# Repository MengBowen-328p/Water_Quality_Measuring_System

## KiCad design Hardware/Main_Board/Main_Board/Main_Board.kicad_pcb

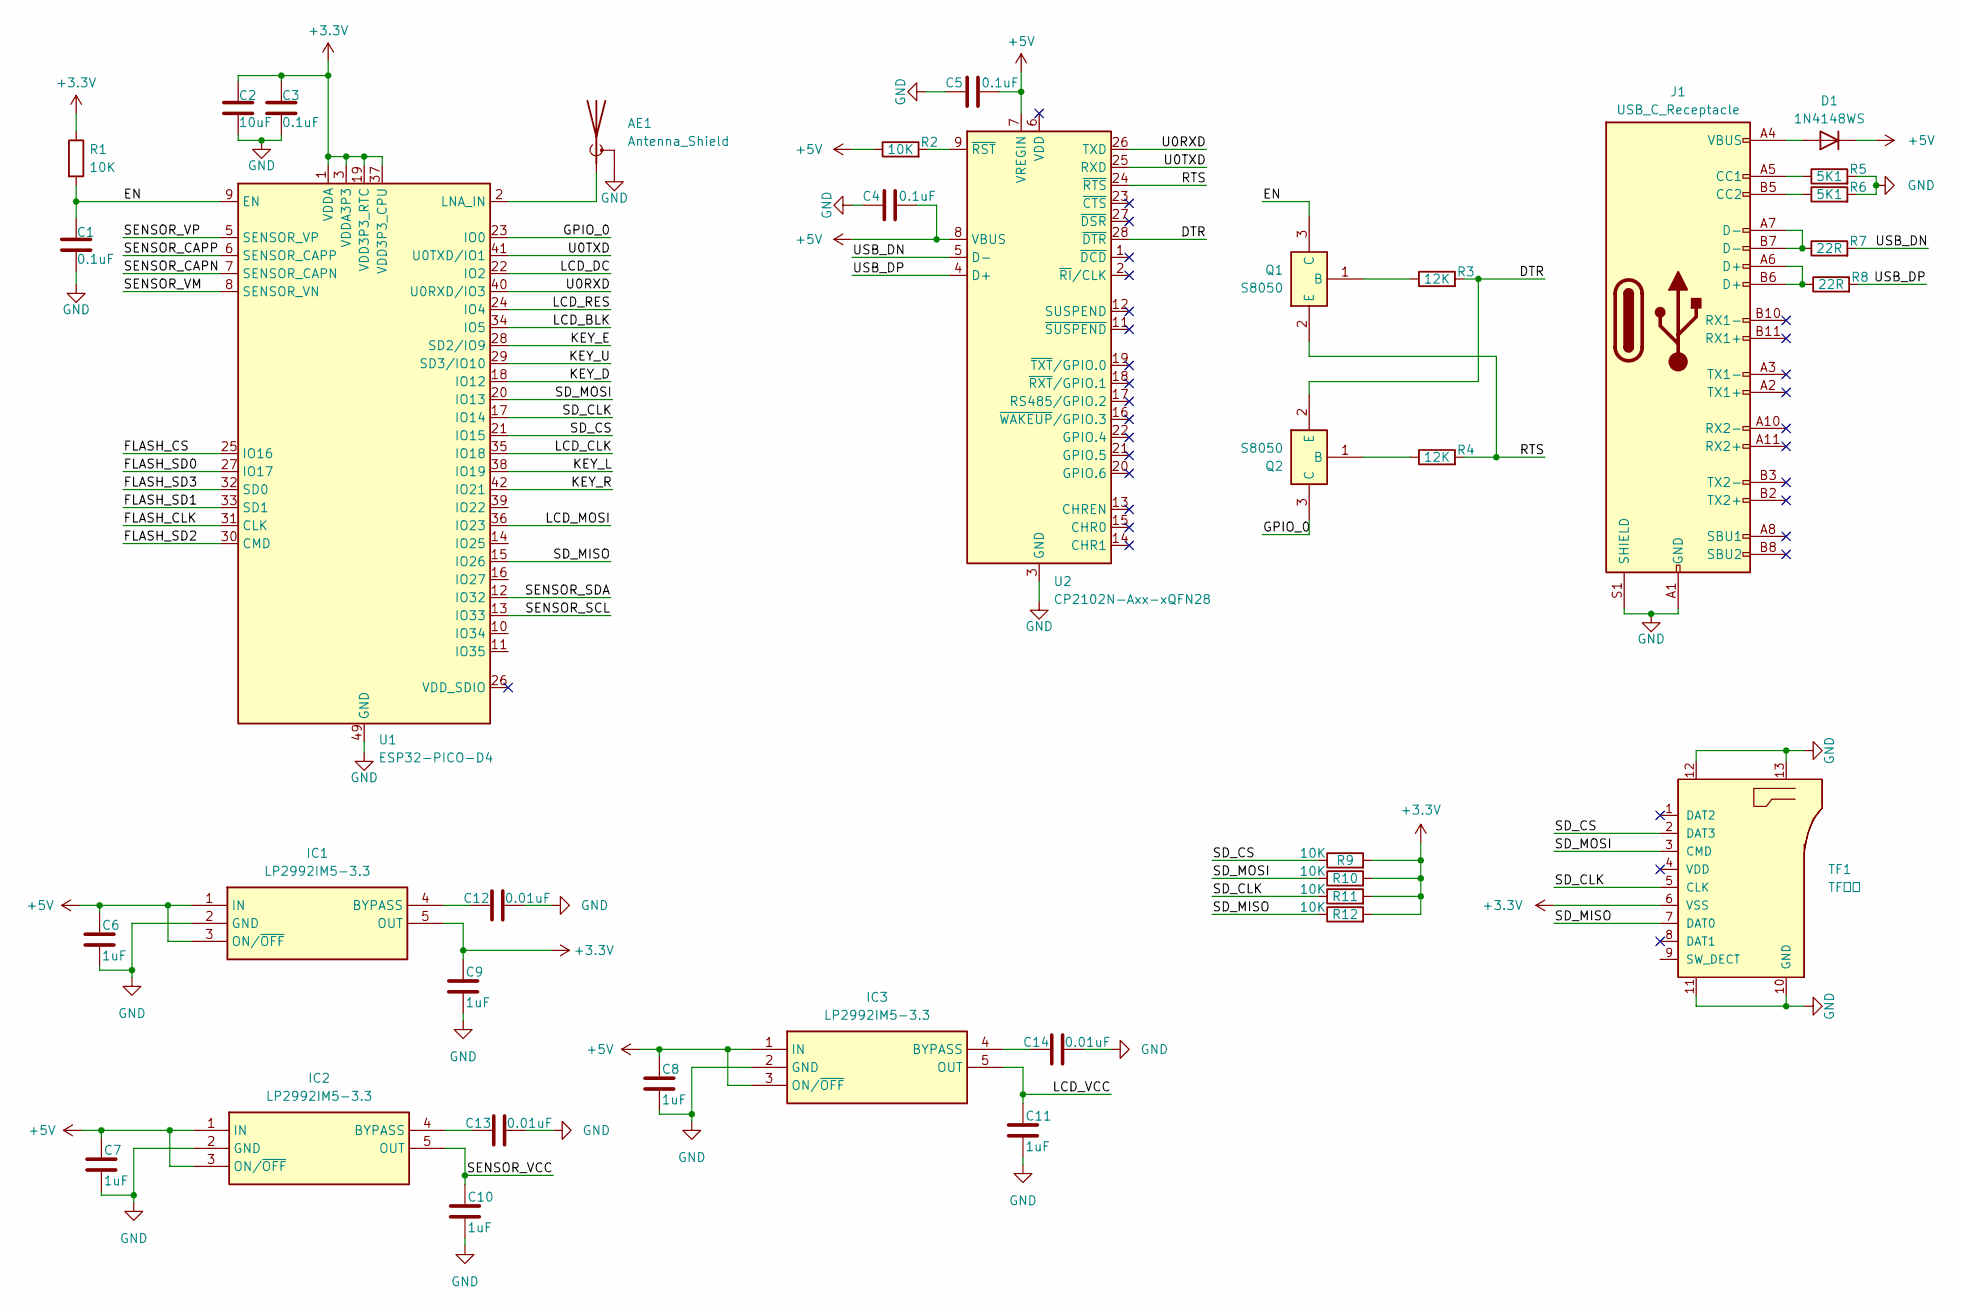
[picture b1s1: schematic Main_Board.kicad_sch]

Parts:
AE1: Antenna_Shield; Johanson_2450AT43F0100
C1, C3, C4, C5: 0.1uF; C_0603_1608Metric
C2: 10uF; C_0603_1608Metric
C6, C7, C8, C9, C10, C11: 1uF; C_0603_1608Metric
C12, C13, C14: 0.01uF; C_0603_1608Metric
D1: 1N4148WS; D_SOD-323
IC1, IC2, IC3: LP2992IM5-3.3; SOT95P280X145-5N; Manufacturer_Part_Number LP2992IM5-3.3; Mouser Part Number 926-LP2992IM5-33
J1: USB_C_Receptacle; USB_C_Receptacle_XKB_U262-16XN-4BVC11
Q1, Q2: S8050; SOT95P240X115-3N; Manufacturer_Part_Number S8050
R1, R2, R9, R10, R11, R12: 10K; R_0603_1608Metric
R3, R4: 12K; R_0603_1608Metric
R5, R6: 5K1; R_0603_1608Metric
R7, R8: 22R; R_0603_1608Metric
TF1: TF卡槽
U1: ESP32-PICO-D4; QFN-48-1EP_7x7mm_P0.5mm_EP5.3x5.3mm
U2: CP2102N-Axx-xQFN28; QFN-28-1EP_5x5mm_P0.5mm_EP3.35x3.35mm

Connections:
+3.3V: C2.1, C3.1, C9.1, IC1.5 (OUT), R1.1, R9.2, R10.2, R11.2, R12.2, U1.1 (VDDA), U1.3 (VDDA3P3), U1.4 (VDDA3P3), U1.19 (VDD3P3_RTC), U1.37 (VDD3P3_CPU), U1.43 (VDDA), U1.46 (VDDA)
+5V: C4.2, C5.2, C6.1, C7.1, C8.1, D1.1 (K), IC1.1 (IN), IC1.3 (ON/~OFF), IC2.1 (IN), IC2.3 (ON/~OFF), IC3.1 (IN), IC3.3 (ON/~OFF), R2.1, U2.7 (VREGIN), U2.8 (VBUS)
/DTR: Q2.2 (E), R3.2, U2.28 (~DTR)
/EN: C1.1, Q1.3 (C), R1.2, U1.9 (EN)
/FLASH_CLK: U1.31 (CLK)
/FLASH_CS: U1.25 (IO16)
/FLASH_SD0: U1.27 (IO17)
/FLASH_SD1: U1.33 (SD1)
/FLASH_SD2: U1.30 (CMD)
/FLASH_SD3: U1.32 (SD0)
/GPIO_0: Q2.3 (C), U1.23 (IO0)
/KEY_D: U1.18 (IO12)
/KEY_E: U1.28 (SD2/IO9)
/KEY_L: U1.38 (IO19)
/KEY_R: U1.42 (IO21)
/KEY_U: U1.29 (SD3/IO10)
/LCD_BLK: U1.34 (IO5)
/LCD_CLK: U1.35 (IO18)
/LCD_DC: U1.22 (IO2)
/LCD_MOSI: U1.36 (IO23)
/LCD_RES: U1.24 (IO4)
/LCD_VCC: C11.1, IC3.5 (OUT)
/RTS: Q1.2 (E), R4.2, U2.24 (~RTS)
/SD_CLK: R11.1, TF1.5 (CLK), U1.17 (IO14)
/SD_CS: R9.1, TF1.2 (DAT3), U1.21 (IO15)
/SD_MISO: R12.1, TF1.7 (DAT0), U1.15 (IO26)
/SD_MOSI: R10.1, TF1.3 (CMD), U1.20 (IO13)
/SENSOR_CAPN: U1.7 (SENSOR_CAPN)
/SENSOR_CAPP: U1.6 (SENSOR_CAPP)
/SENSOR_SCL: U1.13 (IO33)
/SENSOR_SDA: U1.12 (IO32)
/SENSOR_VCC: C10.1, IC2.5 (OUT)
/SENSOR_VM: U1.8 (SENSOR_VN)
/SENSOR_VP: U1.5 (SENSOR_VP)
/U0RXD: U1.40 (U0RXD/IO3), U2.26 (TXD)
/U0TXD: U1.41 (U0TXD/IO1), U2.25 (RXD)
/USB_DN: R7.2, U2.5 (D-)
/USB_DP: R8.2, U2.4 (D+)
GND: AE1.2 (Shield), C1.2, C2.2, C3.2, C4.1, C5.1, C6.2, C7.2, C8.2, C9.2, C10.2, C11.2, C12.2, C13.2, C14.2, IC1.2 (GND), IC2.2 (GND), IC3.2 (GND), J1.A1 (GND), J1.A12 (GND), J1.B1 (GND), J1.B12 (GND), J1.S1 (SHIELD), R5.2, R6.2, U1.49 (GND), U2.3 (GND), U2.29 (GND)
unnamed: AE1.1 (A), U1.2 (LNA_IN)
unnamed: D1.2 (A), J1.A4 (VBUS), J1.A9 (VBUS), J1.B4 (VBUS), J1.B9 (VBUS)
unnamed: C12.1, IC1.4 (BYPASS)
unnamed: C13.1, IC2.4 (BYPASS)
unnamed: C14.1, IC3.4 (BYPASS)
unnamed: J1.A5 (CC1), R5.1
unnamed: J1.B5 (CC2), R6.1
unnamed: J1.A6 (D+), J1.B6 (D+), R8.1
unnamed: J1.A7 (D-), J1.B7 (D-), R7.1
unnamed: Q1.1 (B), R3.1
unnamed: Q2.1 (B), R4.1
unnamed: R2.2, U2.9 (~RST)

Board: 2 copper layers, 36 parts (0 on the bottom side), 29 nets, no tracks yet.

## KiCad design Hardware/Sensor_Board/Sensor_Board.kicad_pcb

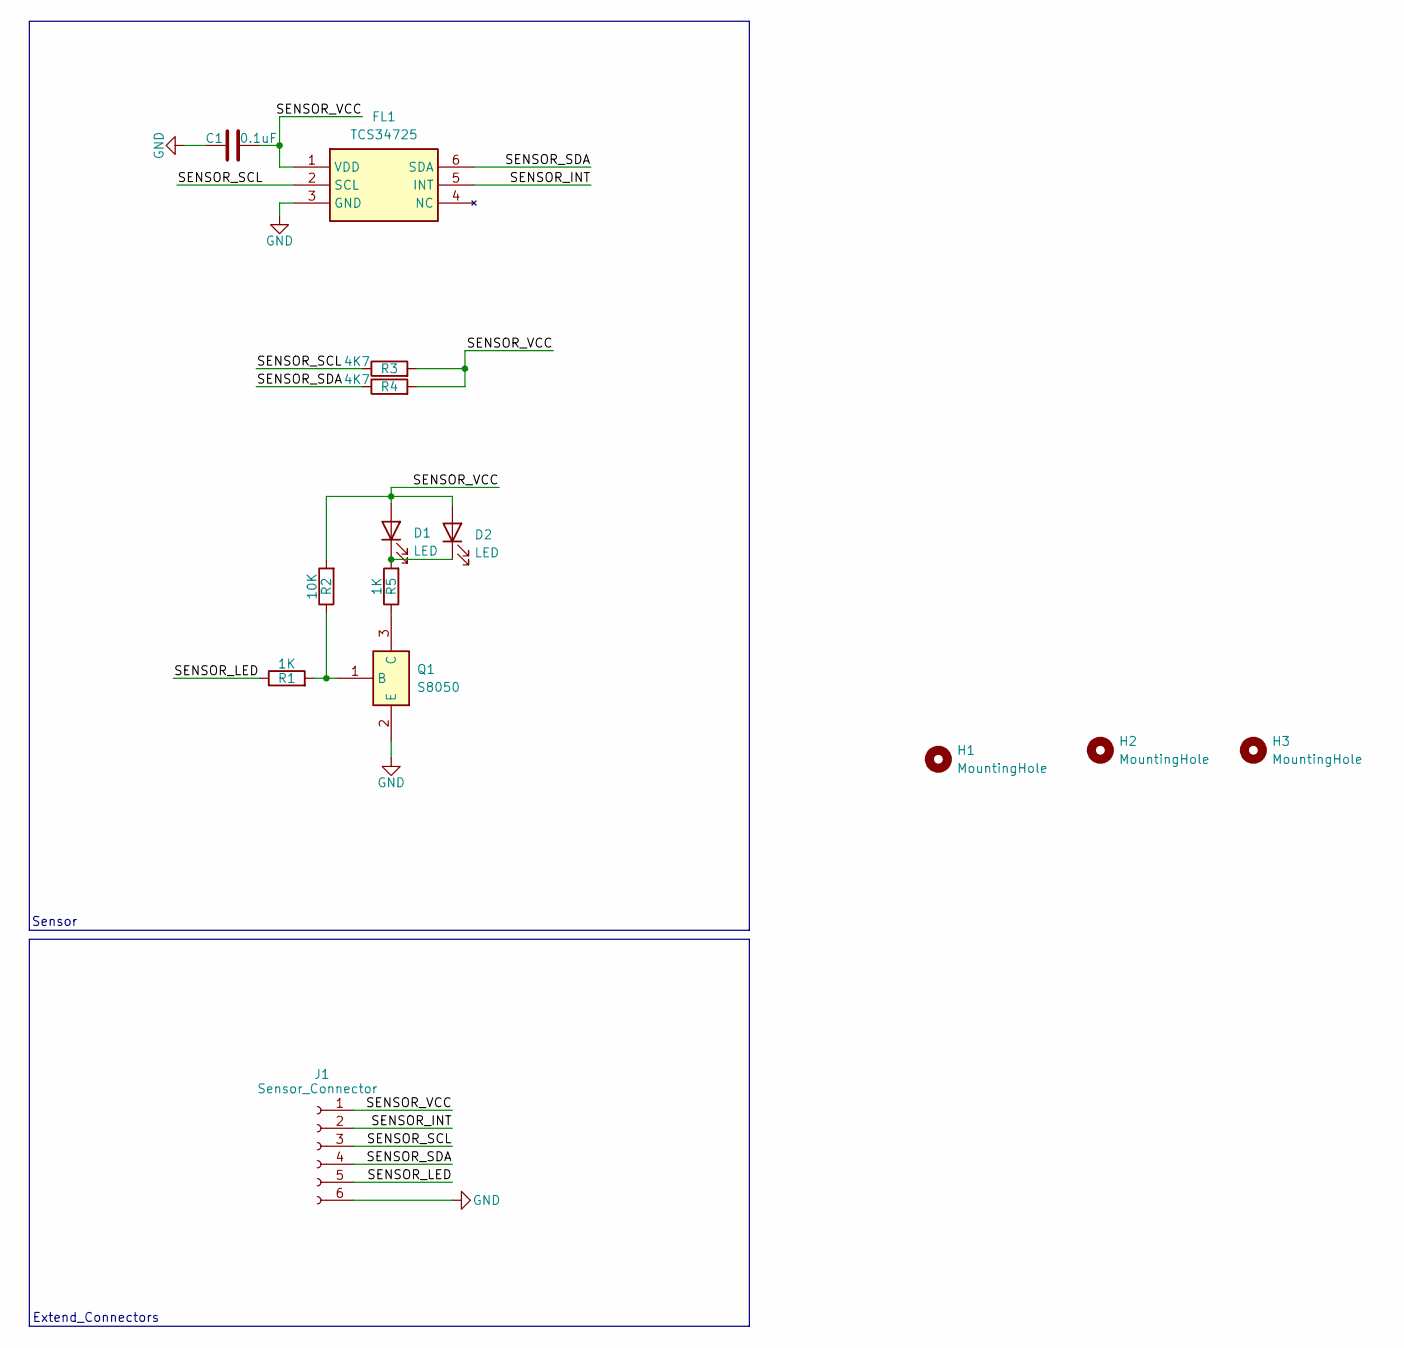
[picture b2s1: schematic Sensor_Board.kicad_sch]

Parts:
C1: 0.1uF; C_0603_1608Metric
D1, D2: LED; LED_RGB_5050-6
FL1: TCS34725; Manufacturer_Part_Number TCS34725
H1, H2, H3: MountingHole; MountingHole_2.2mm_M2
J1: Sensor_Connector; Hirose_FH12-6S-0.5SH_1x06-1MP_P0.50mm_Horizontal
Q1: S8050; SOT95P240X115-3N; Manufacturer_Part_Number S8050
R1, R5: 1K; R_0603_1608Metric
R2: 10K; R_0603_1608Metric
R3, R4: 4K7; R_0603_1608Metric

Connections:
/SENSOR_INT: FL1.5 (INT), J1.2
/SENSOR_LED: J1.5, R1.1
/SENSOR_SCL: FL1.2 (SCL), J1.3, R3.1
/SENSOR_SDA: FL1.6 (SDA), J1.4, R4.1
/SENSOR_VCC: C1.2, D1.2 (A), D2.2 (A), FL1.1 (VDD), J1.1, R2.2, R3.2, R4.2
GND: C1.1, FL1.3 (GND), J1.6, Q1.2 (E)
unnamed: D1.1 (K), D2.1 (K), R5.2
unnamed: Q1.1 (B), R1.2, R2.1
unnamed: Q1.3 (C), R5.1

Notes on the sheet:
Sensor
Extend_Connectors

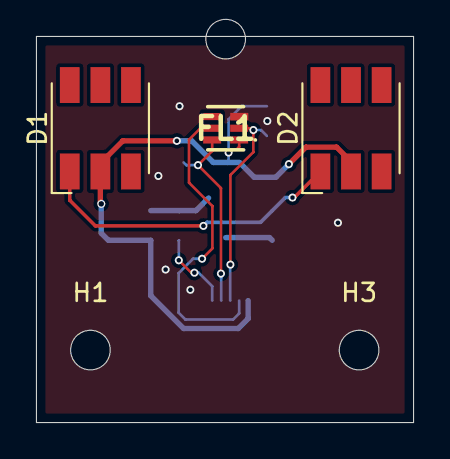
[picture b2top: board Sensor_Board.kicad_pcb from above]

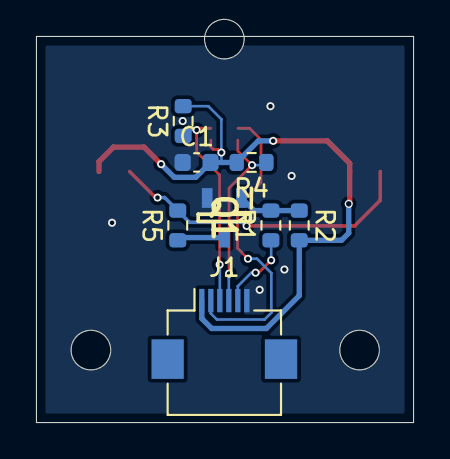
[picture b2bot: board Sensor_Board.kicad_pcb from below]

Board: 2 copper layers, 21.0 x 21.4 mm, 14 parts (8 on the bottom side), 9 nets.

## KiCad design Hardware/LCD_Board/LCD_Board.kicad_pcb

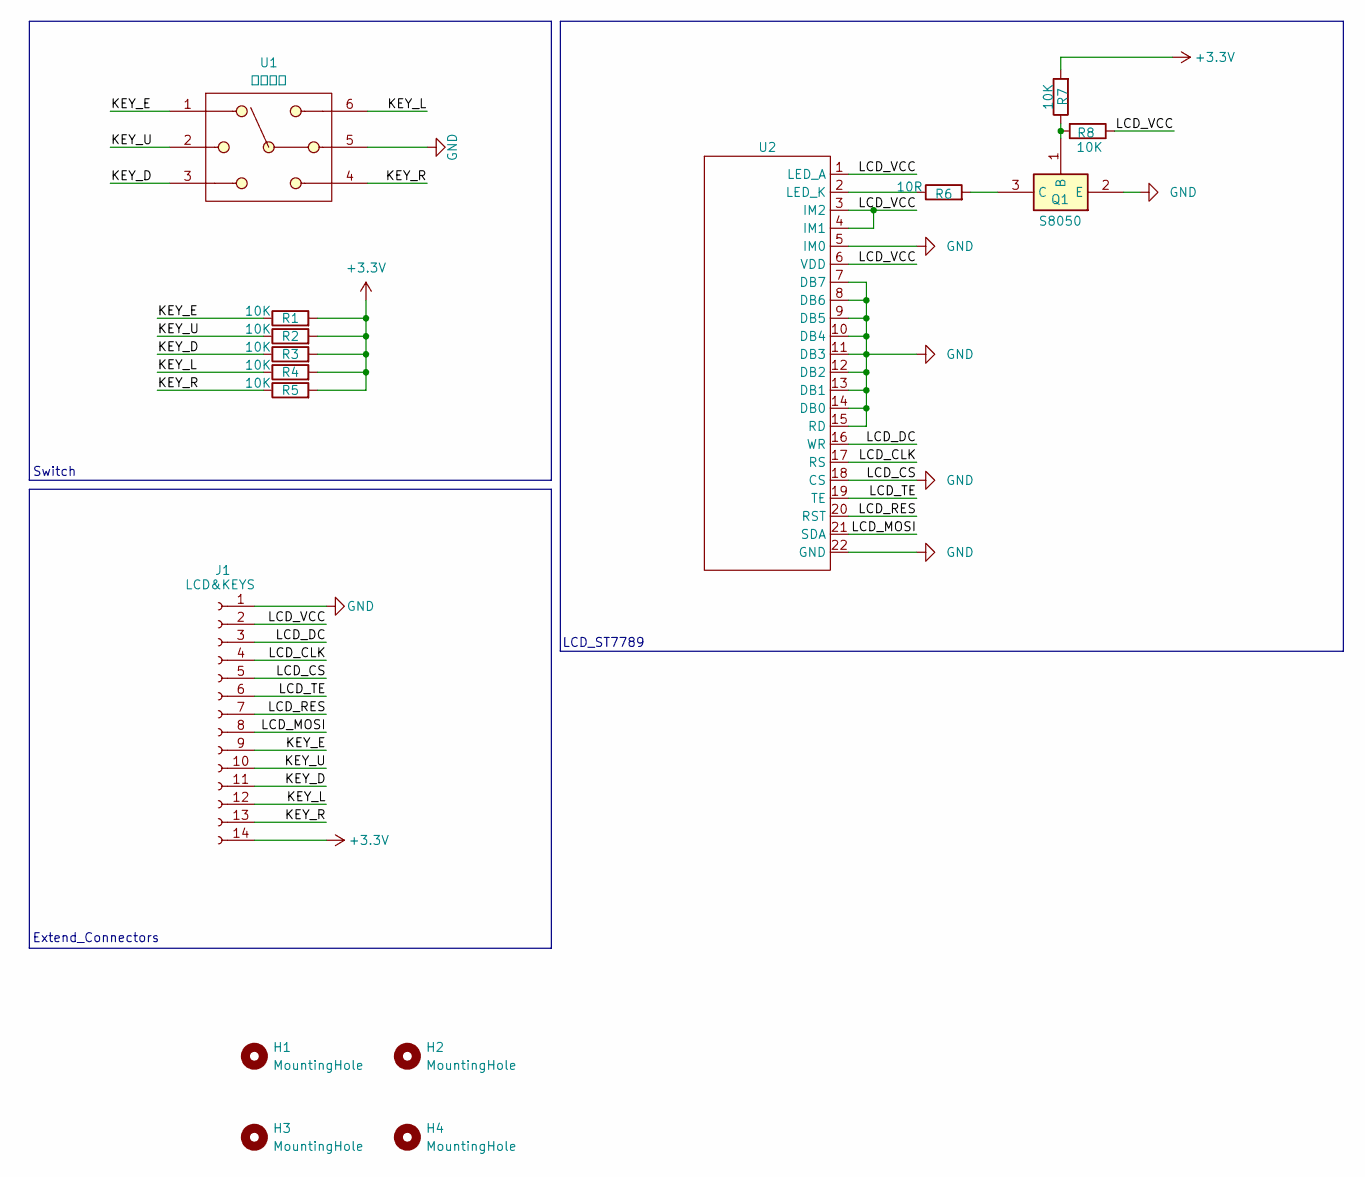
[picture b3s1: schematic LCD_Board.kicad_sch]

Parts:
H1, H2, H3, H4: MountingHole; MountingHole_2.2mm_M2
J1: LCD&KEYS; Hirose_FH12-14S-0.5SH_1x14-1MP_P0.50mm_Horizontal
Q1: S8050; SOT95P240X115-3N; Manufacturer_Part_Number S8050
R1, R2, R3, R4, R5, R7, R8: 10K; R_0603_1608Metric
R6: 10R; R_0603_1608Metric
U1: 五向开关
U2: ZJY200K-IF05

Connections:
+3.3V: J1.14, R1.2, R2.2, R3.2, R4.2, R5.2, R7.2
/KEY_D: J1.11, R3.1, U1.3
/KEY_E: J1.9, R1.1, U1.1
/KEY_L: J1.12, R4.1, U1.6
/KEY_R: J1.13, R5.1, U1.4
/KEY_U: J1.10, R2.1, U1.2
/LCD_CLK: J1.4, U2.17 (RS)
/LCD_DC: J1.3, U2.16 (WR)
/LCD_MOSI: J1.8, U2.21 (SDA)
/LCD_RES: J1.7, U2.20 (RST)
/LCD_TE: J1.6, U2.19 (TE)
/LCD_VCC: J1.2, R8.1, U2.1 (LED_A), U2.3 (IM2), U2.4 (IM1), U2.6 (VDD)
GND: J1.1, J1.5, Q1.2 (E), U1.5, U2.5 (IM0), U2.7 (DB7), U2.8 (DB6), U2.9 (DB5), U2.10 (DB4), U2.11 (DB3), U2.12 (DB2), U2.13 (DB1), U2.14 (DB0), U2.15 (RD), U2.18 (CS), U2.22 (GND)
unnamed: Q1.1 (B), R7.1, R8.2
unnamed: Q1.3 (C), R6.2
unnamed: R6.1, U2.2 (LED_K)

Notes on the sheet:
Extend_Connectors
LCD_ST7789
Switch

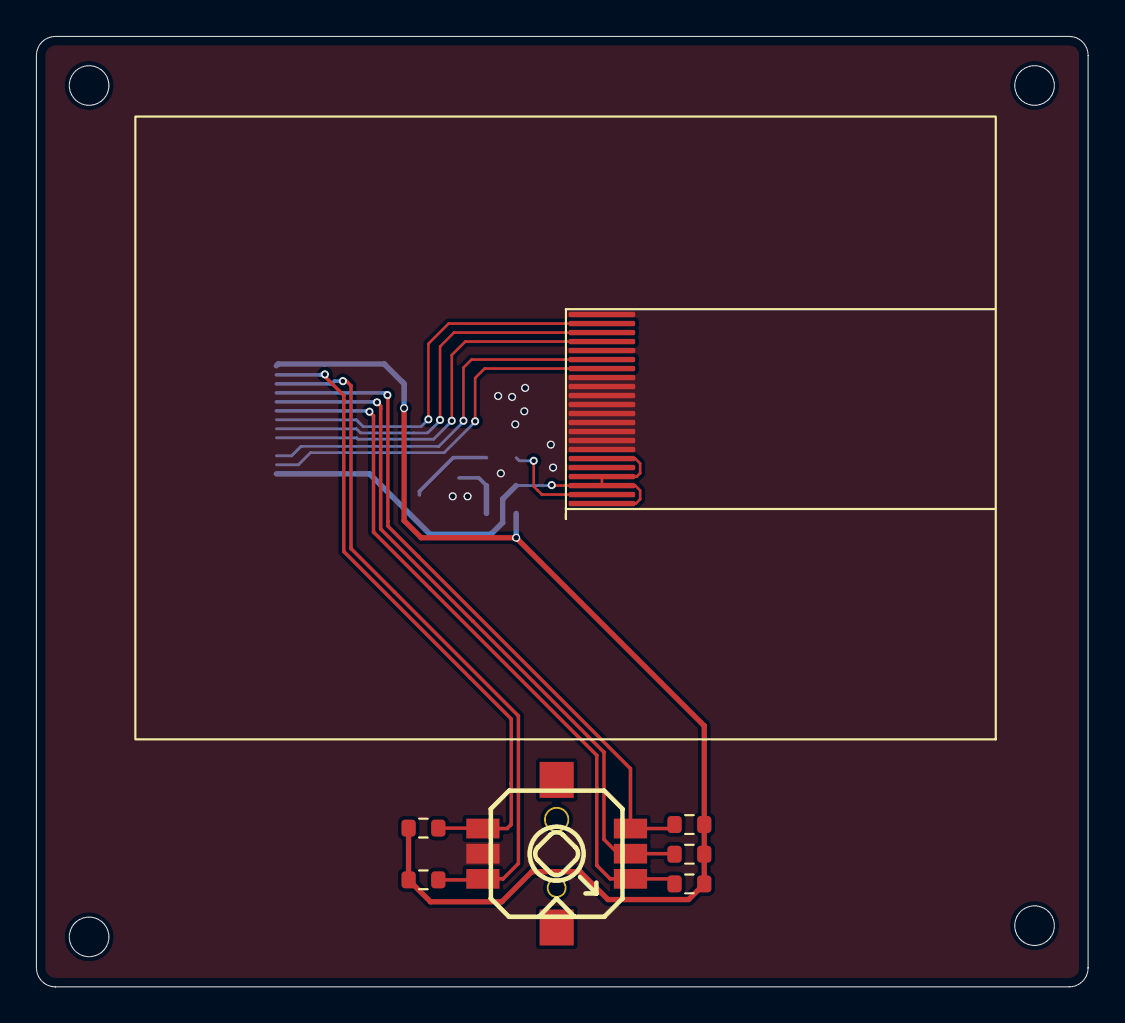
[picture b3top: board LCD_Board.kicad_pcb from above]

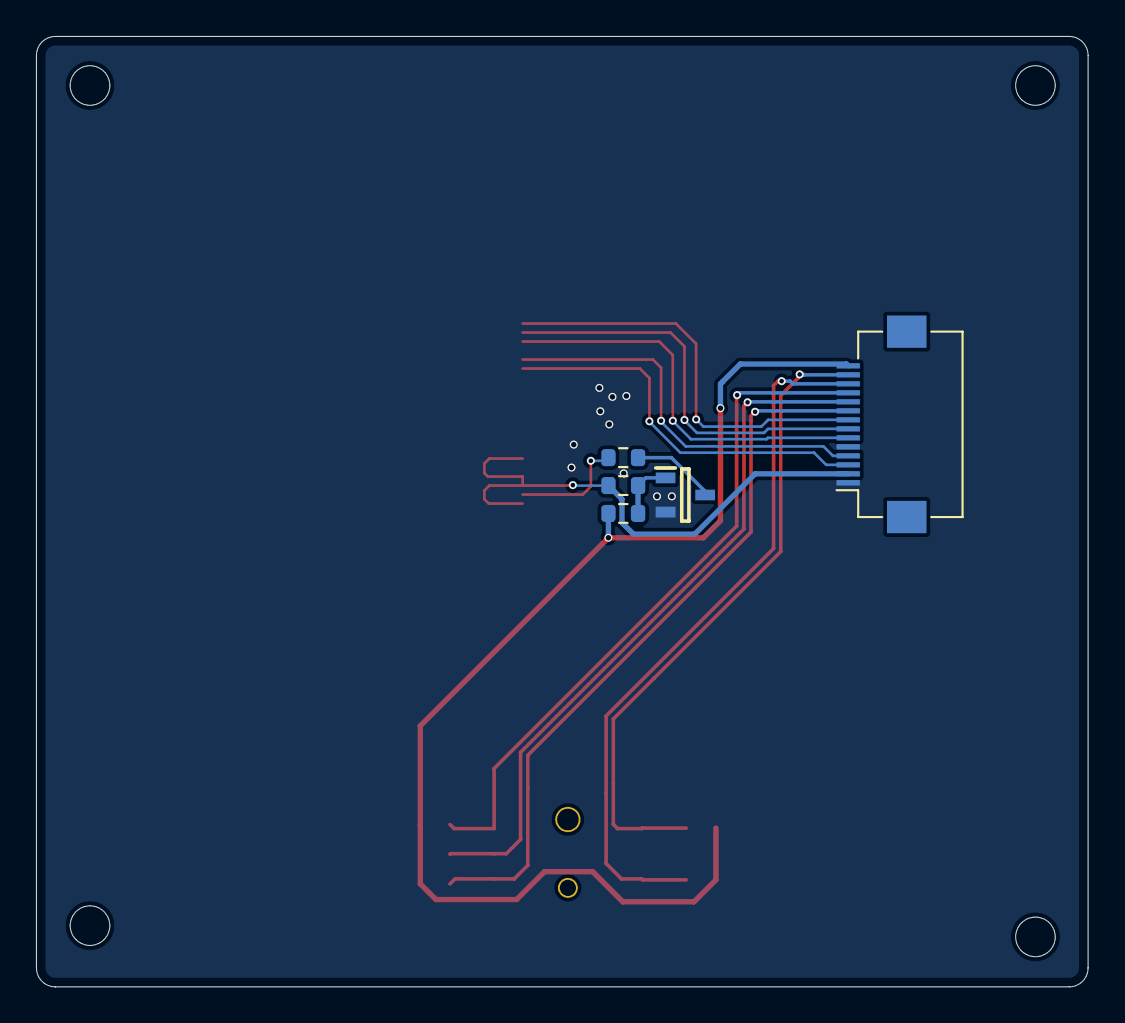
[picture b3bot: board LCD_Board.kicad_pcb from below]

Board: 2 copper layers, 58.4 x 52.8 mm, 16 parts (5 on the bottom side), 16 nets.

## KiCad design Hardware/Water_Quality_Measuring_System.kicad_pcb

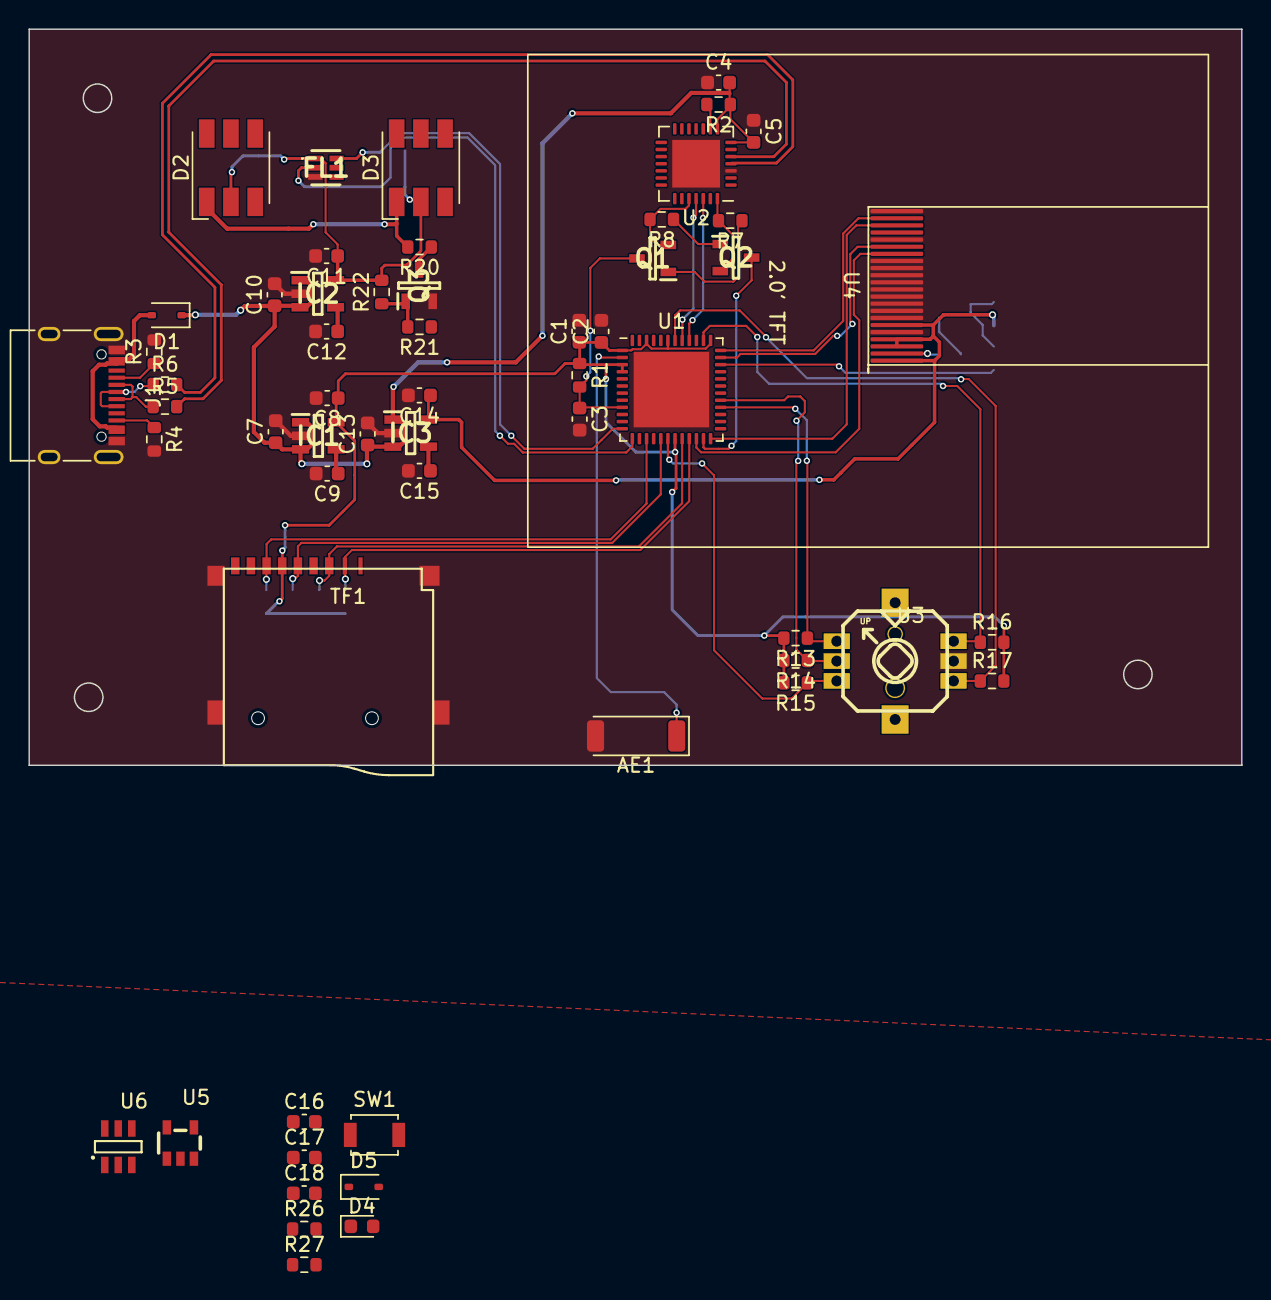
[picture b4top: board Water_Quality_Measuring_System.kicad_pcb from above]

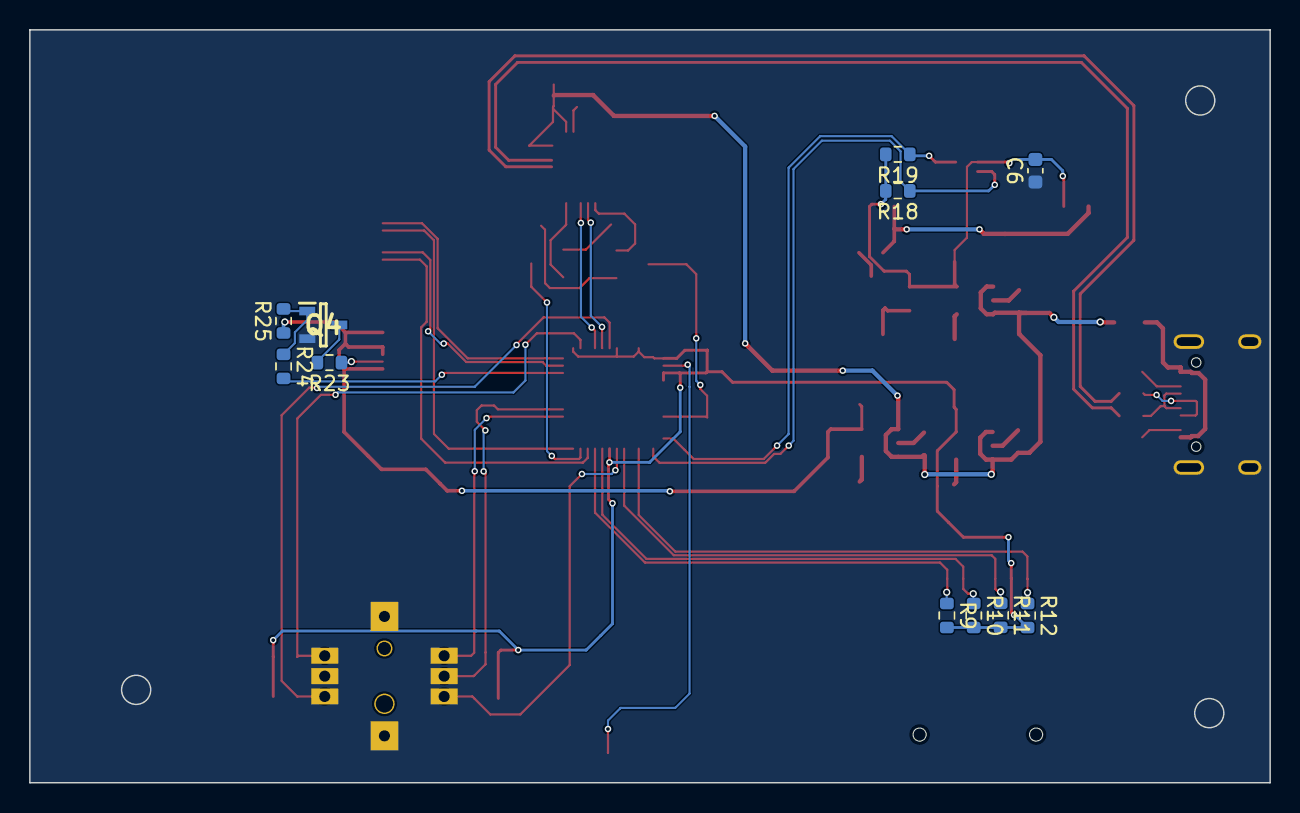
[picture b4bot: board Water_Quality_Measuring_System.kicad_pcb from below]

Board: 2 copper layers, 85.2 x 51.7 mm, 68 parts (11 on the bottom side), 53 nets.

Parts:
AE1: Antenna_Shield; Johanson_2450AT43F0100
C1, C3, C4, C5, C6: 0.1uF; C_0603_1608Metric
C2, C16, C18: 10uF; C_0603_1608Metric
C7, C8, C10, C11, C13, C14, C17: 1uF; C_0603_1608Metric
C9, C12, C15: 0.01uF; C_0603_1608Metric
D1: 1N4148WS; D_SOD-323
D2, D3: LED; LED_RGB_5050-6
D4: LED; LED_0603_1608Metric
D5: 1N5819WS; D_SOD-323
FL1: TCS34725
IC1, IC2, IC3: LP2992IM5-3.3; SOT95P280X145-5N
J1: USB_C_Receptacle; USB_C_Receptacle_XKB_U262-16XN-4BVC11
Q1, Q2, Q3, Q4: S8050; SOT95P240X115-3N
R1, R2, R9, R10, R11, R12, R13, R14, R15, R16, R17, R22, R24, R25, R26: 10K; R_0603_1608Metric
R3, R4: 5K1; R_0603_1608Metric
R5, R6: 22R; R_0603_1608Metric
R7, R8: 12K; R_0603_1608Metric
R18, R19: 4K7; R_0603_1608Metric
R20, R21: 1K; R_0603_1608Metric
R23: 10R; R_0603_1608Metric
R27: 1.66K; R_0603_1608Metric
SW1: Power; SW_SPST_B3U-1000P
TF1: TF卡槽
U1: ESP32-PICO-D4; QFN-48-1EP_7x7mm_P0.5mm_EP5.3x5.3mm
U2: CP2102N-Axx-xQFN28; QFN-28-1EP_5x5mm_P0.5mm_EP3.35x3.35mm
U3: 五向开关
U4: ZJY200K-IF05
U5: TP4055-42-SOT25-R; SOT-23-5_L2.9-W1.6-P0.95-LS2.8-BL
U6: EC190707; EC190707_STD

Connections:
+3.3V: C1.1, C2.1, C8.1, IC1.5 (OUT), R1.1, R9.2, R10.2, R11.2, R12.2, R13.2, R14.2, R15.2, R16.2, R17.2, TF1.6 (VSS), U1.1 (VDDA), U1.3 (VDDA3P3), U1.4 (VDDA3P3), U1.19 (VDD3P3_RTC), U1.37 (VDD3P3_CPU), U1.43 (VDDA), U1.46 (VDDA)
+5V: C4.2, C5.2, C17.2, D1.1 (K), R2.1, R26.1, U2.7 (VREGIN), U2.8 (VBUS), U5.4 (VCC)
/BAT+: C16.2, C18.2, U5.3 (BAT), U6.5 (VDD)
/BAT_OUT: C7.1, C10.1, C13.1, IC1.1 (IN), IC1.3 (ON/~OFF), IC2.1 (IN), IC2.3 (ON/~OFF), IC3.1 (IN), IC3.3 (ON/~OFF), U6.1 (OUT)
/DTR: Q2.2 (E), R7.2, U2.28 (~DTR)
/EN: C3.1, Q1.3 (C), R1.2, U1.9 (EN)
/GPIO_0: Q2.3 (C), U1.23 (IO0)
/KEY_D: R15.1, U1.18 (IO12), U3.3
/KEY_E: R13.1, U1.28 (SD2/IO9), U3.1
/KEY_L: R16.1, U1.38 (IO19), U3.6
/KEY_R: R17.1, U1.42 (IO21), U3.4
/KEY_U: R14.1, U1.29 (SD3/IO10), U3.2
/LCD_BLK: R24.2, U1.34 (IO5)
/LCD_CLK: U1.35 (IO18), U4.17 (RS)
/LCD_DC: U1.22 (IO2), U4.16 (WR)
/LCD_MOSI: U1.36 (IO23), U4.21 (SDA)
/LCD_RES: U1.24 (IO4), U4.20 (RST)
/LCD_VCC: C14.1, IC3.5 (OUT), R25.1, U4.1 (LED_A), U4.3 (IM2), U4.4 (IM1), U4.6 (VDD)
/RTS: Q1.2 (E), R8.2, U2.24 (~RTS)
/SD_CLK: R11.1, TF1.5 (CLK), U1.17 (IO14)
/SD_CS: R9.1, TF1.2 (DAT3), U1.21 (IO15)
/SD_MISO: R12.1, TF1.7 (DAT0), U1.15 (IO26)
/SD_MOSI: R10.1, TF1.3 (CMD), U1.20 (IO13)
/SENSOR_SCL: FL1.2 (SCL), R18.1, U1.13 (IO33)
/SENSOR_SDA: FL1.6 (SDA), R19.1, U1.12 (IO32)
/SENSOR_VCC: C6.2, C11.1, D2.2 (A), D3.2 (A), FL1.1 (VDD), IC2.5 (OUT), R18.2, R19.2, R22.2
/U0RXD: U1.40 (U0RXD/IO3), U2.26 (TXD)
/U0TXD: U1.41 (U0TXD/IO1), U2.25 (RXD)
/USB_DN: R5.2, U2.5 (D-)
/USB_DP: R6.2, U2.4 (D+)
GND: AE1.2 (Shield), C1.2, C2.2, C3.2, C4.1, C5.1, C6.1, C7.2, C8.2, C9.2, C10.2, C11.2, C12.2, C13.2, C14.2, C15.2, C16.1, C17.1, C18.1, D5.1 (K), FL1.3 (GND), IC1.2 (GND), IC2.2 (GND), IC3.2 (GND), J1.A1 (GND), J1.A12 (GND), J1.B1 (GND), J1.B12 (GND), J1.S1 (SHIELD), Q3.2 (E), Q4.2 (E), R3.2, R4.2, R27.2, SW1.1, TF1.10 (GND), TF1.11, TF1.12, TF1.13, U1.49 (GND), U2.3 (GND), U2.29 (GND), U3.5, U4.5 (IM0), U4.7 (DB7), U4.8 (DB6), U4.9 (DB5), U4.10 (DB4), U4.11 (DB3), U4.12 (DB2), U4.13 (DB1), U4.14 (DB0), U4.15 (RD), U4.18 (CS), U4.22 (GND), U5.2 (GND), U6.2 (GND)
unnamed: AE1.1 (A), U1.2 (LNA_IN)
unnamed: D1.2 (A), J1.A4 (VBUS), J1.A9 (VBUS), J1.B4 (VBUS), J1.B9 (VBUS)
unnamed: D2.1 (K), D3.1 (K), R20.2
unnamed: D4.2 (A), R26.2
unnamed: D4.1 (K), U5.1 (CHRG)
unnamed: D5.2 (A), SW1.2, U6.3 (KEY)
unnamed: C9.1, IC1.4 (BYPASS)
unnamed: C12.1, IC2.4 (BYPASS)
unnamed: C15.1, IC3.4 (BYPASS)
unnamed: J1.A5 (CC1), R3.1
unnamed: J1.B5 (CC2), R4.1
unnamed: J1.A6 (D+), J1.B6 (D+), R6.1
unnamed: J1.A7 (D-), J1.B7 (D-), R5.1
unnamed: Q1.1 (B), R7.1
unnamed: Q2.1 (B), R8.1
unnamed: Q3.1 (B), R21.2, R22.1
unnamed: Q3.3 (C), R20.1
unnamed: Q4.1 (B), R24.1, R25.2
unnamed: Q4.3 (C), R23.2
unnamed: R2.2, U2.9 (~RST)
unnamed: R23.1, U4.2 (LED_K)
unnamed: R27.1, U5.5 (PROG)

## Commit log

2024-01-10 Finished PCB Layout
2024-01-10 Init Firmware
2024-02-28 Finished Main Board PCB
2024-02-28 Finished All PCB
2024-03-01 Finished GUI Firmware
2024-03-02 Porting Input Device
2024-03-04 Init Indev
